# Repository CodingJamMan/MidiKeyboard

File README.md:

# MidiKeyboard
This is a pcb design for a midi keyboard that uses electricity to act as a fake piano making noises through a speaker.
This is a project fpor half life hack club feel free to use anything you find here.

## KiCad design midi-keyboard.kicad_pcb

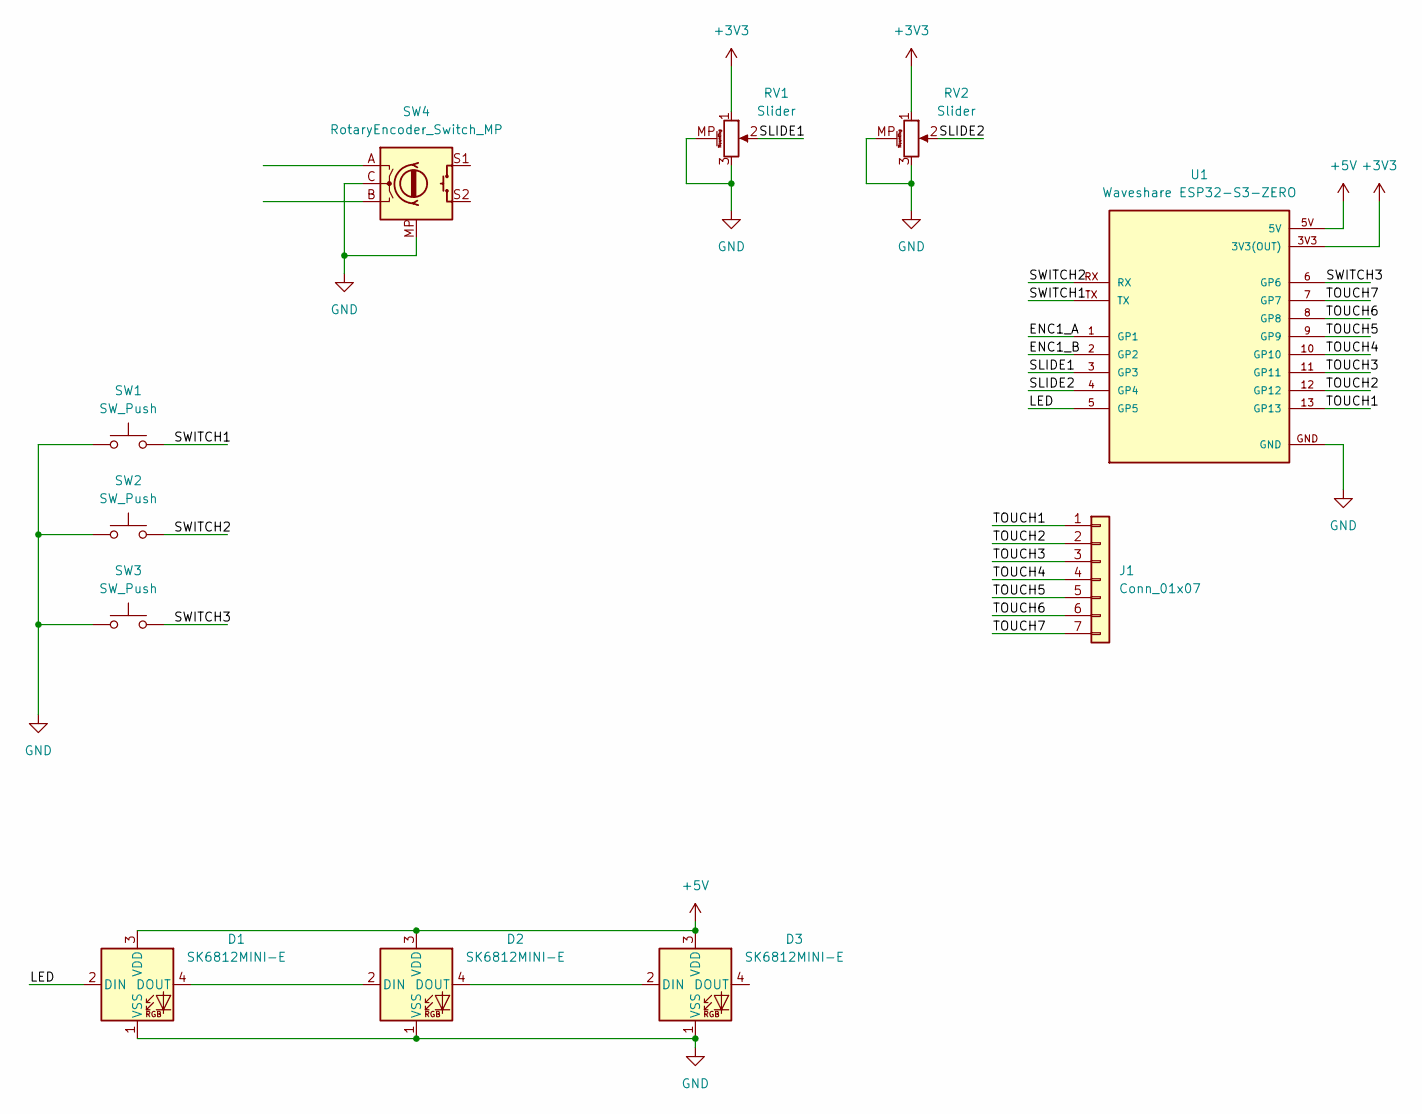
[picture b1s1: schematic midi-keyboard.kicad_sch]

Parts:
D1, D2, D3: SK6812MINI-E; LED_SK6812MINI-E_3.2x2.8mm_P1.5mm_ReverseMount
J1: Conn_01x07; Untitled
RV1, RV2: Slider; Potentiometer_Bourns_PTA3043_Single_Slide
SW1, SW2, SW3: SW_Push; Kailh Choc Low-Profile Switches
SW4: RotaryEncoder_Switch_MP; RotaryEncoder_Alps_EC11E-Switch_Vertical_H20mm
U1: Waveshare ESP32-S3-ZERO; Waveshare ESP32-S3-Zero; PARTREV NA

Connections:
+3V3: RV1.1, RV2.1, U1.3V3 (3V3(OUT))
+5V: D1.3 (VDD), D2.3 (VDD), D3.3 (VDD), U1.5V
/ENC1_A: U1.1 (GP1)
/ENC1_B: U1.2 (GP2)
/LED: D1.2 (DIN), U1.5 (GP5)
/SLIDE1: RV1.2, U1.3 (GP3)
/SLIDE2: RV2.2, U1.4 (GP4)
/SWITCH1: SW1.2, U1.TX
/SWITCH2: SW2.2, U1.RX
/SWITCH3: SW3.2, U1.6 (GP6)
/TOUCH1: J1.1, U1.13 (GP13)
/TOUCH2: J1.2, U1.12 (GP12)
/TOUCH3: J1.3, U1.11 (GP11)
/TOUCH4: J1.4, U1.10 (GP10)
/TOUCH5: J1.5, U1.9 (GP9)
/TOUCH6: J1.6, U1.8 (GP8)
/TOUCH7: J1.7, U1.7 (GP7)
GND: D1.1 (VSS), D2.1 (VSS), D3.1 (VSS), RV1.3, RV1.MP (MountPin), RV2.3, RV2.MP (MountPin), SW1.1, SW2.1, SW3.1, SW4.C, SW4.MP, U1.GND
unnamed: D1.4 (DOUT), D2.2 (DIN)
unnamed: D2.4 (DOUT), D3.2 (DIN)

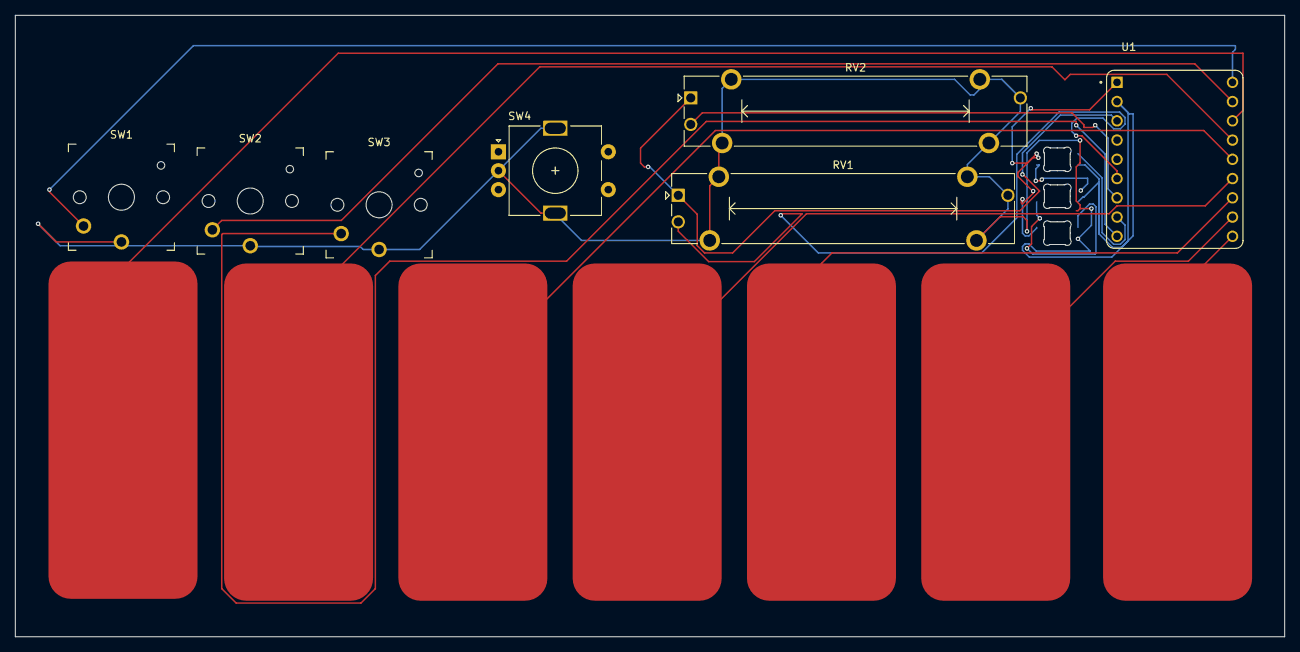
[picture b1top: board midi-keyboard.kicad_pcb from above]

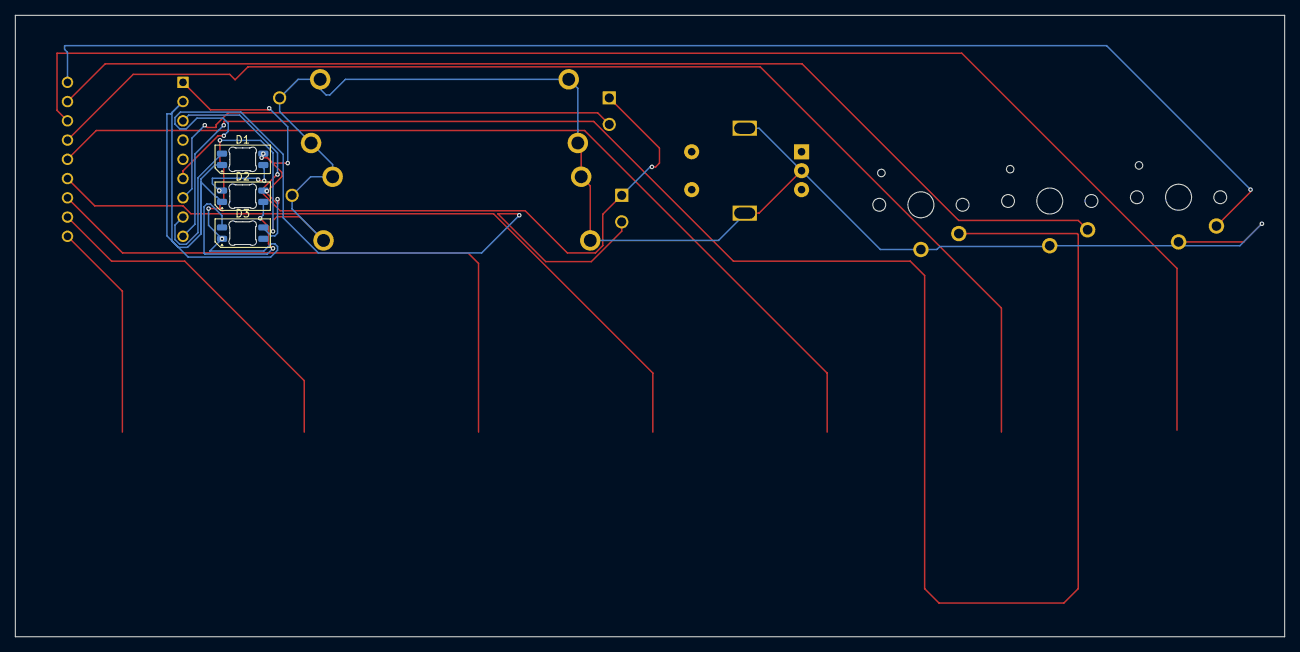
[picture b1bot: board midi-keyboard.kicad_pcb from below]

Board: 2 copper layers, 167.5 x 82.0 mm, 11 parts (3 on the bottom side), 18 nets.
